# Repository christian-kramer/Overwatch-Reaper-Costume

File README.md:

# Overwatch-Reaper-Costume
Design files for Reaper's costume from Overwatch

---

This repo is my first for an actual "product" I've designed. It's a step forward in my exploration of embedded systems and circuit design, expanding on both my previous [Light Sensor](https://github.com/christian-kramer/Light-Sensor) and [STM32F407 Familiarization](https://github.com/christian-kramer/STM32F407-Familiarization) projects.

This project came about due to a need from a friend of some electronics and 3D models for a custom costume she was making: Reaper, from the videogame Overwatch.

Specifically, Reaper's dual shotguns. The requirements were:

1. All the red lights on the guns *(two spots underneath the barrel, one on the side-switch, one on the front underneath the barrels, and one near the top of the gun facing backwards towards Reaper)* need to be illuminated with a lighting effect accurate to the in-game look.
2. The barrels need to illuminate when the trigger is pulled, to mimic shots being fired.
3. Sound effects of a shot firing need to play every time the trigger is pulled, with no more than 4 shots per gun firing before the "reload" sound effect is played. Both guns need to reload at the same time, so if one is empty before the other, it needs to wait for the last shot to be fired from the other gun. Additionally, voice lines Reaper says in the video game after a kill need to play during the reload... making sure to play a different voice line each time.
4. Power is to be provided by two AA batteries per gun, due to space constraints in the handle.

So... Logically, thinking about this, I know I need some lights, a speaker, a radio, a microcontroller fast enough to handle the task of producing sound somehow, and a circuit board to hold everything together.

Cool! Sounds like a fun project. Let's start by figuring out what kind of lighting looks good.

LEDs are an obvious first thought, since they're so cheap and ubiquitous. But they're also very bright, and has a point-like look, even when diffused. Even after throwing everything I could think of at a standard 5mm red LED, I just couldn't get it to achieve the same look as the game. I tried thinking of other things that might produce a much deeper, richer red... A while ago, I had seen something cool on Adafruit called EL Wire, that might work. It's got a really, really nice effect:

But it requires a clunky inverter, and I'm dubious about how it'll show up in bright light.

I started looking around for other solutions, and stumbled upon this:

["Side-glow Fiber Optic Cable."](https://www.amazon.com/light-fiber-source-illuminator-Yellow/dp/B01M68WEUS) It looks great, and it's not electrical in nature! You can cut it to length, and whatever color LED you put into it is what you'll get out. So I ordered some, to try it out with the red LED. Unfortunately, it just wasn't bright enough. Too much light was being emitted from the sides of the LED, and not enough was going directly into the fiber optic cable. I was certain that if I could just get the LED to focus all of its energy into it, it would be bright enough. The first thing that comes to mind when trying to get light into a single point is a laser, so I started researching red laser diode modules and how to use them.

Turns out, all they need is 3 volts and a constant current supply of around 20 milliamps, and you can get [10 for $6.00 on Amazon](https://www.amazon.com/Laser-Diode-Module-650nm-10PCS/dp/B0166JFLES/ref=sr_1_3?keywords=laser+diode+module&qid=1562638198&s=gateway&sr=8-3) (with Prime, even!).

I ordered some, and I was blown away at how great it looked with the fiber optic cable!

My phone's camera doesn't do it justice. To the human eye, the light is perceived as very intense red. Not blindingly so, but it definitely looks a whole lot like what the video game shows for the lighting effects! I guess we're using lasers in our project.

A side-note about these laser modules: They're supposed to be supplied with an active constant-current power supply, but I found that a 22Ω resistor was plenty sufficient for stabilizing the current. These are for lighting effects, not scientific measurement.

My next step was to rip an existing solid 3D gun model off of thingiverse and hollow it out to find space for all the parts, and also figure out how to get the trigger to move instead of just being static like on the original model.

After much work figuring out how to make everything fit, and mount securely inside, I came up with this configuration:

In the handle are the two AA batteries, and behind the trigger is the microswitch I'm using to detect actuation and also provide the necessary "springiness" to give the feeling of a nice click when depressed. In blue is the speaker, positioned on a sliding tray above the decorative vent holes I drilled out to pass sound through to the outside world. Towards the front of the gun is the circuit board I still had yet to design, but I made it plenty big enough (8cm x 10cm) so that I should have no trouble fitting all the components I need onto it. On the circuit board, I modeled a little laser-holder to keep the side-glow fiber optic cable attached to the lasers, and the lasers attached to the board. Just a couple 3mm screw holes holding a couple clamshells together, with enough tension to make sure nothing moves. Simple, and easy to 3D print.

Speaking of circuit boards, I need to design one! But I need to figure out what to put on it first... I've got the lasers' chunk of real-estate dished out, but I still need to determine exactly what else I need to provision for. Well, I need a microcontroller to start. I think the ol' PIC10F220's out of the question for this one... I need something with a little more oomph. I remember really liking the STM32F407 when I was screwing around with my dev board, but that's probably a bit overkill for a project like this. I want a Goldilocks processor... so in the spirit of trying to use the bare minimum in my projects, and because I used a PIC in my last project, I'm going to look for a bottom-of-the-barrel STM32. Let's see what eBay's got.

I mean... that's nice and all, but that's still a lot of pins at a very high clock speed. I said bottom-of-the-barrel, darn it!

Now we're talking! It's not even in a quad flat package, it's dual-inline with only 20 pins! Let's load up CubeMX and see what it's got for features. (probably not a whole lot)

Actually, not bad! It's got an ADC, support for *both* I2C and SPI, 5 general-purpose timers plus a watchdog timer, and a real-time clock. Not bad for a 20-pin part. I think we have a winner for our microcontroller.

Also, as a bonus, dev boards are dirt-cheap.

Alright, I think now's a good time to tackle the hard part: sound.

I know that I use file formats like WAV and MP3 to store sound on my PC, but is any of that readable to a microcontroller of this simplicity? I needed to learn a lot more about how these formats work under the hood, and how other people have gone about playing sound on devices like the Arduino.

Apparently, since a WAV file is uncompressed, it represents what is called "PCM Audio", or "Pulse-Code Modulation Audio". This means that the bytes in a WAV file sequentially represent amplitude data of the audio waveform - the thing you see when you open something in Audacity or the like. Depending on the sample rate and resolution, this can be as simple as one byte representing an aplitude of anywhere from 0 to 255, played one after the other, 8000 times per second for an 8-bit, 8kHz audio file.

Here's a good visualization:

Each line is 1/8000 of a second apart (sample rate of 8kHz) and the value at each line can be anywhere from 0 to 255 (8-bit resolution). Turn those numbers into voltages that move a speaker cone, and baby, you've got audio.

Now how the heck do I get this thing to talk to a speaker? It certainly doesn't do so natively, like the STM32F407 does... gotta figure that one out on my own. Somehow, I need to get that waveform out to an amplifier. Most times, that's done with something called a Digital to Analog converter, or DAC, which you'll hear thrown around on various products' descriptions. But in the spirit of bare-minimum, I tried to see if I could use Pulse-Width Modulation combined with a filtering circuit to create the analog waves.

I'm just going to say right now, that I couldn't get that to work no matter how hard I tried. I'm going to have to bookmark that technique for later. For now, I'm saying "screw it" and using a DAC. But which DAC should I use?

A fairly popular one amongst the hobbyist community, produced in droves in China, is called the MCP4725. 

It's a nifty little thing, in the same size package as the the PIC10F220 I'm so familiar with. 12-Bit Resolution, rail-to-rail output which means it'll give me the full swing of 0v to 3.3v, and it supports High-Speed I2C which is more than enough to cover the 8kHz sample rate plus I2C frame data. Perfect! Now I gotta find an amplifier, because I really don't trust this thing to drive a speaker the size of what I need.

Now, every good EE has heard of the legendary LM386. Since 1969, it's been powering hobbyist and professional audio projects where "sounds good enough" reigns supreme. It's simple, yet versatile, and does what it's supposed to without a whole lot else. It takes an input, makes it louder, and gives you an output for an 8Ω speaker. If you need it even louder, put a capacitor between pins 1 and 8. Sound too staticy? Put a capacitor between pin 7 and ground. Boom, done. Loud. Happy? Good.

These chips are so common, even the knockoffs have knockoffs. You can buy buckets of them for next to nothing, which makes them great for this project and possibly future ones since I'll probably have plenty laying around.

One problem, though... It needs a minimum of 4v to work, and everything else I've got is 3.3v. Looks like I need two power rails... remember that, for later.

Wait, sorry, I see two problems... the LM386 input is expecting a voltage between 0 and 0.4v, not 0 and 3.3v like my DAC is putting out. Anything above 0.4v is going to get clipped, which means I need to figure out how to scale the audio. I want to make use of the full 12-bit resolution of the MCP4725, so I'm thinking maybe scaling the output of the DAC using some analog circuitry before it gets to the LM386 might be a good idea.

A common tactic for scaling an analog signal like this is to use two resistors in a configuration called a "voltage divider".

If we want 3.3v (the upper limit of the DAC) to correspond with 0.4v (the upper limit of the amplifier input), and we start with a known resistor value of 150kΩ for Z1 (because that's a standard resistor value that I know is produced), we get a nominal Z2 value of 20.69kΩ, which is not a standard resistor that is produced. Luckily, 20kΩ is, and that's "close enough for government work."

I'd also like to explain why I'm choosing resistors in this range of values... the answer, is because I just need a voltage reference for the LM386. I don't want to waste unnecessary battery power heating up resistors, but I also don't want so much resistance that the voltage reference isn't responsive enough for my purposes. These are in a sweet spot between both.

So after all of my dev boards arrived in the mail, and I pulled an LM386 out of an old door alarm, I ended up building this:

The STM32 communicates over High-Speed I2C to the MCP4725, which outputs the PCM WAV file to voltages anywhere between 0 to 3.3v depending on the wave amplitude at that "frame" of the sound file. That 0 to 3.3v signal gets coupled to the voltage divider in the reverse-"L" shape by a 10nF capacitor to help smooth out the "jumps" in the 8kHz audio, then finally gets sent to the LM386 input pin. The LM386 output pin gets coupled to the 8Ω speaker by a pretty big capacitor. Here, I'm using a 330µF electrolytic to remove the DC bias from the amplifier, so the speaker cone goes through its whole range of motion. Additionally, I put a high-pass filter on the output pin to chop off some unwanted low-frequency noise.

The sound file itself is stored on the STM32, compiled from a C character array that I just iterate through 8000 times per second in a for loop.

Unfortunately, due to how small the storage on-board the STM32 is, I found only one voice line of Reaper's that was short enough to fit on it! In order to store *all*  of them, I'm going to need some external storage.

I thought to myself... "Hm... flash storage has been getting pretty dense and cheap, lately. I wonder what kind of chips are out there that might store the amount of data I'm looking for."

I looked into Micro SD Cards, but even for a 2GB card it took over 100 milliamps! Holy cow, I don't have that kind of overhead with these two AA batteries! And 2GB is *way* overkill for what I need. I had to find something smaller, and lower-power.

Eventually, my friend ended up finding this:

The Macronix MX25L1606EM2I, a 2MB SPI flash chip capable of exchanging data at very high speeds, at very low power. The cool thing about SPI flash chips is that their form factor is pretty much standardized, as well as their pinout and (for the most part) their instruction set... so in the future, if I theoretically wanted to switch out this chip for a larger one, or a different manufacturer, it should be a drop-in replacement. Pretty convenient!

But unlike a Micro SD Card, I can't just plop this into my PC and drag files onto it... This is just bare memory, I needed to be able to talk to it somehow.

Looking around on eBay, I found a pretty highly-rated Flash IC programmer that supported both SPI and I2C chips called the CH341A.

The MX25L1606EM2I can't plug directly into the ZFI socket on the programmer, so I made sure to find one that included this little "clamp" to hold onto the 8 pins of the flash chip.

The software for it looks like this:

And I gotta say, after changing the language from Chinese, it was pretty much plug-and-play. (With the exception of the diagram in the lower left being WRONG! The chip should be rotated 180 degrees, in that same 8-pin slot.) The programmer talked to the chip just fine, and I could key-in values at whatever memory addresses I wanted.

So... I got the chip to talk to my computer, and store data successfully. But how about reading it from the microcontroller?

Reading into the datasheet, the command structure for reading from the chip is:

1. Pull the Chip-Select pin low.
2. Send it `0x03` in the first byte of data. This is to instruct the chip that we intend to read from it, and we are about to give it an address in the next 3 frames.
2. Send it the first byte of the 6-byte address.
3. Send it the second byte of the 6-byte address.
4. Send it the third byte of the 6-byte address. Note: after these are all sent, the chip will start reading off not only that byte, but every consecutive byte until it reaches the end.
5. Finally tell it to shut up by pulling the Chip-Select pin high.

And that, in theory, should work. There's two other pins on the chip that are of interest: Write-Protect, and Hold. Write-Protect does what you'd expect, and Hold stops the entire chip from doing anything. From my adventures diving into EE forums, I learned that those pins aren't necessary for normal operation, and can just be left unconnected.

But... when I tried reading a memory address on the flash chip from the STM32, it wouldn't respond! I was getting no data back at all!

So, to troubleshoot, I hooked the chip back up to the CH341A, but this time using DuPont jumper wires, and verified that it could talk to the PC. Then, I pulled the Write-Protect jumper out to see if that was the culprit... No dice, the flash chip was still acting normally. Next, I pulled the Hold jumper out... and bingo! I got a Read Error from the software saying that the chip wasn't responding.

So, instead of leaving Hold unconnected like I originally did, I tried tying it to ground with that jumper... And the read error went away! It was behaving normally again.

On the microcontroller side of things, I tried using another jumper to tie Hold to ground while leaving Write-Protect floating... and suddenly, I got the byte of data I was expecting!

My breadboard prototype now looked like this:

After uploading a larger WAV file to the flash chip than would fit on the STM32, I tried reading each byte and outputting it to the DAC fast enough to play the voice line. The result was actually pretty promising, and sounded decent considering the mediocre speaker I was using.

Next challenge: the radio.

So, after a cursory glance at what other people are using for their low-cost RF needs for Arduino  projects and whatnot, I was consistently pointed towards the nRF24L01 module.

These are about a buck a pop on Amazon, with Prime shipping included. Interestingly enough, these *also* communicate over SPI... which means I now have to make sure that the MX25L1606EM2I and nRF24L01 will play nice together on the same line. After all, with the Hold pin needing to be tied to ground, which it shouldn't have to be, it very well may not.

See... SPI isn't addressed. You have to expressly tell each chip, "HEY! I'm talking to you." And sometimes, when finished talking to that chip, it won't release the MISO line like it's supposed to, which prevents other chips from talking.

SD Cards are apparently notorious for exhibiting that behavior when operating in SPI mode, so... yeah, I'm glad I didn't use one on this project.

A common workaround for this is to put a device called a "tri-state buffer" on the problem device, which then forcefully disengages the MISO line for that device when the Chip-Select line goes high, thus allowing other devices to talk.

So the only way to figure out if the MX25L1606EM2I was a problem device, was to try it on the same SPI line as the nRF24L01.

I tacked on a radio module to my breadboard, and whipped up a little battery-powered stand-alone nRF24L01 + STM32 project.

Then, I wrote some code that did the following:

1. Battery-powered module transmits to waiting sound-breadboard module that it should start playing the soundbyte from the flash chip, which is indicated by the blue LED on the sound-breadboard module turning on.
2. The sound-breadboard module instantly transmits back to the battery-powered module to turn on its LED, indicating that bidirectional communication is possible.
3. After the soundbyte finishes playing on the sound-breadboard, it instructs the battery-powered module to turn off its LED. This indicates a successful handover from radio, to flash chip, to radio... I.E. both devices are capable of releasing the MISO line without issue.
2. Once the battery-powered module has turned off its LED, it instantly instructs the sound-breadboard module to do the same.

The result of these four transactions should yield two devices that turn on, and off their LEDs seemingly in perfect synchronization, while also proving that neither device is holding the MOSI line hostage.

And... here it is in action:

[Dual-SPI Device Test Video](https://i.gyazo.com/60b7cc6970f24641ac8ad5783b88ba2e.mp4)

Success! No tri-state buffer needed.

Additionally, to improve sound-quality, I added some more filtering on the output pin. For such low-cost and low-power parts, it was starting to sound *really* good... and loud!

This pretty much constituted the entirety of the project... sound, lights, bidirectional communication... I feel like I'm forgetting something, though.

Oh, right. Power.

Yeah, I forgot... I gotta run *all this* off of just 2 AA batteries. Since I need 3.3v for most of my electronics, and 5v for the LM386, but the AA batteries provide *at most* 3v... I need to boost the voltage somehow.

I did some digging for any battery-management chips that may exist, that are cheap enough for my project... and stumbled upon a magical unicorn called the AAT1217.

Easy-to-use with just 6 pins, an external inductor, and some resistors to set the output voltage (and an external schottky diode if you're setting it above 4.5v), this baby will squeeze every last drop of juice out of your choice of either a single AA battery, two AA batteries, or a single disposable Lithium-Ion battery, with up to 93% efficiency... all in the same package as the PIC10F220 and the MCP4725. Perfect!

My strategy was to set this to 5v to supply the LM386 with what it needs, and then use a linear regulator to step it back down to 3.3v. In the grand scheme of things, that's a trivial change, and any regulator worth its salt should be able to handle that with almost no energy loss.

My regulator of choice: AMS1117

Funny enough, these things are in the dev boards I ordered... as well  as like, every Arduino ever made. Pretty common, and very cheap!

With all this planned out, I set to work creating the schematic for the whole circuit board. Something I made sure to include was a jumper to cut power to all the lasers, so that I could completely remove the risk of damaging my eyes when I was working on the board.

Dang, that's a whole lot more complicated than my first board design. Time to lay it out!

I tried to compartmentalize different parts... power in the lower right, audio amplifier in the top right, all the connectors on the right edge so they point towards the back of the gun... laser holder on the bottom, with 3mm drill holes... 5 connectors, all in a row for the 5 lasers, with the one that can be blinked marked with a \*. I had trouble routing all the traces away from the STM32, so I flipped it to the backside of the board and broke it out with a bunch of vias, so I had enough room to work.

After a few weeks, the boards arrived in the mail:

Fun fact: Matte Black doesn't cost any more than Green, at JLCPCB. Man, it looks good! And the CK is so shiny...

Because these boards are so complex, and I never tested the AAT1217 before designing it in... I decided it would be best to assemble this in parts, starting with the lower right power circuitry and the lasers.

And... Hey! It works!

This was with fresh batteries, supplying very nearly 3v... But for fun, I tested this with batteries that wouldn't even run my analog wall clock, and the laser powered up just fine at the same brightness as the fresh batteries. Whether or not the amplifier will still work with batteries this dead remains to be seen.

The next parts of the board, I assembled in steps. The very next thing I soldered was the STM32. I wanted to make sure that was getting clean enough power to talk to the ST-Link, over the programming header on the board. The "RST" pin you see towards the bottom of the header isn't actually needed. I included it just in case I needed to force-reset the chip for any reason, but during normal programming/debugging operation, the STM32 accepts a "software reset" - a special sequence of bits that tells the internal firmware of the STM32 that it's time to  go into reset mode. When powered off the batteries, the ST-Link only needs 3 wires: DIO, CLK, and GND.

Next was the MCP4725 and associated 4.7kΩ I2C pull-up resistors. I wanted to make sure that, before I assembled the amplifier, I was getting a good output from the DAC to limit how much troubleshooting I'd have to do, should this board not produce sound as expected.

After I verified that the MCP4725 was outputting the voltages I told it, at speeds comparable to what I need for clear audio, I went ahead and assembled the  amplifier. I had a test from earlier that I already made to play a small soundbyte from the internal STM32 flash... After loading that up, and plugging in the speaker... it sounded great!

Now that I knew sound worked at the most basic level, I knew I could go ahead and get the flash chip programmed with all the voice lines, and try playing WAV files from that.

Essentially, I just stacked everything together end-to-end... but I knew that by just doing that, it'd be hard to see in the hex editor where individual soundbytes were in the file. So, I came up with a way to delineate each one by driving the amplitude up to 255 between each voice line. In audacity, it looks like this:

In the hex editor, it looks like this:

That wall of FF's you see there is my marker for where the sound data ends, and at the end of the wall is the next voice line. It continues on past the bottom of the window a bit, so it's impossible to miss while I'm scrolling. This way, I've eliminated guesswork for where each individual sound file is located... and I don't have to re-guess if I decide to switch out or remove a voice line from the chip. It's plain-as-day to see what I'm working with. Also, to quash any concerns about "wasting bytes"... These voice lines barely use 1/4 of the chip's total capacity. I've got plenty of room to spare for making things easy for myself.

After proving that I could play audio from the chip through the DAC and amplifier... I moved on to soldering the radio onto the SPI bus. Once the radio was on, I loaded up another program of mine that tests bidirectional communication with another radio on a breadboard, to trigger playing a sound file. Something unusual happened, though... Unlike my breadboard tests with an (in theory) identical circuit, the assembled board refused to transmit back to the other radio, after the sound file finished playing. "This is odd," I thought, because in the program, it's supposed to wait for the broadcast... What's going on?

My initial thought was that the power requirements were too much... but the issue persisted even *after* I unplugged the speaker. What gives? My next thought was that maybe I really did need that tri-state buffer, after all. Unpredictable chips causing weird behavior, and such... But after some tests with reading the status register of the nRF24L01, I proved that the flash chip was handing over control of the MISO line like it should. What in the world was going on here?! Faulty radio? Using my breadboard prototype, I was quickly able to test all 9 other radios in my pack of 10 from Amazon, and all worked just fine. The likelihood that I picked the single bad one at random from the bag was too small for me to really consider... Due to the proximity of the radio's pins to the flash chip, it would be too  risky to remove it... So I opted to try using jumper wires to test the radio I had soldered onto my board. I had difficulty getting one jumper on the MISO pin, due to a glob of solder getting in the way. After heating it up, and moving it down to the base of the pin, an idea popped into my head: "What if that just fixed it, right there?"

So I turned it on, and boom! Bidirectional communication restored. All it was, was a bad solder joint on one of the data pins! What a relief. With that final outlying problem solved, I had in my hands an (almost) fully working board. All that was left was to get the LEDs, transistors, and the Trigger connector soldered, and crimp some more JST connectors onto my lasers!

Next, I needed to get the front-facing LEDs, transistors, and trigger switch port added on.

Oddly enough, I think the transistors ended up being the most difficult part to solder by far. I've actually never soldered a TO-92 package component before, so I was woefully unprepared for the challenges I encountered. These things dissipate as much heat as possible by design... and when a glob of solder comes into contact with one of the legs, it pretty much instantly cools and solidifies before it has a chance to bond with the board. This leaves you with legs that *look* soldered... but actually have no electrical contact with the board whatsoever, and can be moved as easily as a loose tooth. Reworking is almost impossible, because any heat you add to the problem-solder gets immediately transferred to the transistor casing. Too much heat kills the transistor, which means you have to heat it up an absurd amount to get the solder glob to even budge. Adding more solder to try to rectify the problem doesn't work either, because I've found it almost always ends up contacting a neighboring pad.

I learned all this after killing around 6 transistors on the second board, trying to get them to stick.

When you do kill a transistor by trying to solder it too much, it is extremely difficult to remove. Because the legs cool very quickly, pulling the entire length out through the hole isn't really an option. I had to resort to cutting the legs as short as possible, and then simultaneously heating them up, and torquing them through with brute force. Actually, on that second board, a fragment of the Base pin of a broken transistor got permanently stuck in the hole, and I was forced to solder the new leg directly to the resistor.

As far as soldering the rest of the legs... I came up with a technique that seemed to work pretty reliably, and it's one that I'll likely use for future TO-92 soldering; if you cut the legs flush with the holes *before* soldering, and just "cap" each one with a small glob of solder... it mitigates almost every issue mentioned above. You still only get "one shot," and it still has a good chance of making contact with a neighboring pad, but it's the best I've been able to come up with so far.

After this was all said and done with, I fired up the second board to make sure it worked as intended. But... it didn't, in one very weird aspect. One of the LEDs on the front was really, really dim when it was supposed to be off... and only got *dimmer* when it was supposed to be on! What in the world?! I was convinced I had managed to solder the transistors withoug killing them, this time... so what was happening? I measured the voltage at the base resistor of both of the other transistors... 3.3v, just as they should be. Then, I measured it at the base resistor of the problem transistor... 0v! The problem must be up-stream somewhere. Is the other end of the resistor getting 3.3v? Yes... and that goes directly to the microcontroller. And... that pin looks fine, from a quick visual inspection. Uh oh, did my transistor-shenanigans end up killing a GPIO pin? A quick reading of the pin with my multimeter shows that it's putting out 3.3v on command... so, no, it's fine. Must be a problem with the pad. But, quickly checking the continuity of the resistor showed that it was good all the way through! How could this be?!

After much troubleshooting, the answer was a little embarrassing... the very, *very* slight pressure from the multimeter probe was forcing the pin to make contact with the pad, and give a false impression of reliable continuity. One swipe from my fine-tipped soldering iron connected the pad properly, and the LED lit up and turned off just fine.

That's the one thing I really dislike about these STM32s... The dual-inline package has such fine pins that it seems to almost never go down without needing some sort of tedious rework. I'll have to try out a quad flat package in a future project to see if that's easier.

In the meantime, I've also figured out an even easier/more reliable method of soldering TO-92's... just use solder paste, and heat them up like you would an SMD component. The solder paste flows exactly where it needs to, and provides a very secure bond with the board. No hassle, and almost guaranteed to not kill the transistor.

Eventually, I got all 4 boards finished up, and ready to program! Still gotta finish all those lasers and cables up, though.

Meanwhile on the mechanical side, things were (literally) starting to take shape.

Here are the bottoms of the handles that house part of the trigger assembly, and form the very bottom of the battery housing...

And here are some various small parts for the internals of the gun, like the Speaker Tray, PCB Tray, the two halves of the 5-Laser-Holder that mounts to the two holes on the PCB, and some general support material.

Some bigger parts have also been printed, such as one half of the front barrel which houses the PCB, and the decorative handle on the back.

Inside, the slot for the tray, and the cavity for the front-facing fiber optic cable look great!

Back to PCB-land for a moment; it's firmware time!

Now, the only human interface our guns have is the trigger... so that means that the logical distinction of which of the two boards is in charge of making decisions like what channel to communicate on, when to reload, and which voice line to play after the reload needs to be made in software, and not with a jumper or DIP switch or something.

The best way I could think of to describe how the two boards need to behave was to make a flowchart:

What I've made here is called a "Finite-State Machine", which is a machine that can be in exactly one of a finite number of states at any given time. This computational paradigm is, in practice, insanely reliable and thus used extensively in industrial automation and "black-box" consumer electronics.

Check out my [`main.c`](https://github.com/christian-kramer/Overwatch-Reaper-Costume/blob/master/Electrical/Source/Main%20Firmware/Src/main.c) showing how I implemented this logic. Commented to enhance readibility.

And, to see this whole thing in action, check out this video I made of all 4 boards operating in the same general vicinity with no interference:

[https://youtu.be/M1ywswBbeoI](https://youtu.be/M1ywswBbeoI)

With the electronics completed, it was back to getting all the parts 3D printed.

A second 3D printer was purchased to help cope with the amount of printing, an Ender 3 Pro by Creality. After some setup, it was off to the races (for only $200!)

Eventually, all the pieces needed for one of the guns were printed!

It was time to do a test fit to see how everything went together. While it looks like a very complicated assembly process, the pieces are actually quite intuitive to put together since they're all so unique.

See, very simple. It's not glued together yet, this is just a test-fit to see how it all sizes up and if there's any parts that need a little TLC. But everything fit nice and snug, and lined up the first time!

And, of course, ruler for scale:

Other parts for the costume started to get printed as well, like various pieces of Reaper's 4 belts:

And, here it is for size:

Next, it was time for sanding and a round of paint! Time to make these pieces *really* look good!

Before:

After:

Black was the chosen base coat, to be followed by silver in applicable areas.

Together, they make a really neat effect!

All of the parts came out really shiny, and they look amazing.

Next, it was time for the big prints! The gauntlets were to be printed in two parts... a smaller, lower wristpiece... and a gigantic upper forearm piece that would take many hours and have a relatively high probability of failure.

But... dang! Fresh off the printer, the first one looks amazing! It's a little angular due to having to manually stitch some polygons together in Cinema 4D, but that'll clean up after some sanding.

So, arms are coming along nicely, but now it's time for the legs! We've got some boots to make. But I don't feel like making a boot from scratch, so let's find an existing pair to build off of. We had an old pair of motorcycle boots that resembled the shape of Reaper's boots that we could add parts to. But... the parts in their current form won't fit the boot perfectly, and I'm not willing to sit there printing adjustment after adjustment just to hone in on the right shape. I need to know that the part I'm printing is going to fit, 100%. So, how do we do this?

An idea I had was to use photogrammetry to "scan" the boots into Cinema 4D, and then mold the pieces virtually before printing.

We took video of all angles of the boots to give Agisoft Photoscan every possible detail to work off of. In After Effects, I keyed out the pink backdrop to generate an alpha channel mask for every frame of the video, which was then exported as a PNG sequence with alpha channel. That gave us about 1000 camera angles to work with, which in my experience should be plenty to get an accurate model.

After a few nights of computation, Photoscan spit this out:

Beautiful! I can work with this.

After a bit of work, I made this in Cinema 4D:

Yeah, it clips a little bit... but boots aren't completely solid, so these parts should fit.

And... It definitely looks like they will! No wasted PLA plastic here. This method totally works!

Meanwhile, while all this is going on, the PCBs have arrived at their final destination and are ready to be mated to the 3D printed gun for the first time.

And... there it is! Sound works, the LEDs line up with the barrels properly, and it's definitely loud and bright enough!

The connection between the radio and microcontroller on the PCB is a little shaky, though, which is something I encountered on my bench tests... It may be necessary to do a "revision 2" of the boards in order to remedy the issue and make it more reliable.

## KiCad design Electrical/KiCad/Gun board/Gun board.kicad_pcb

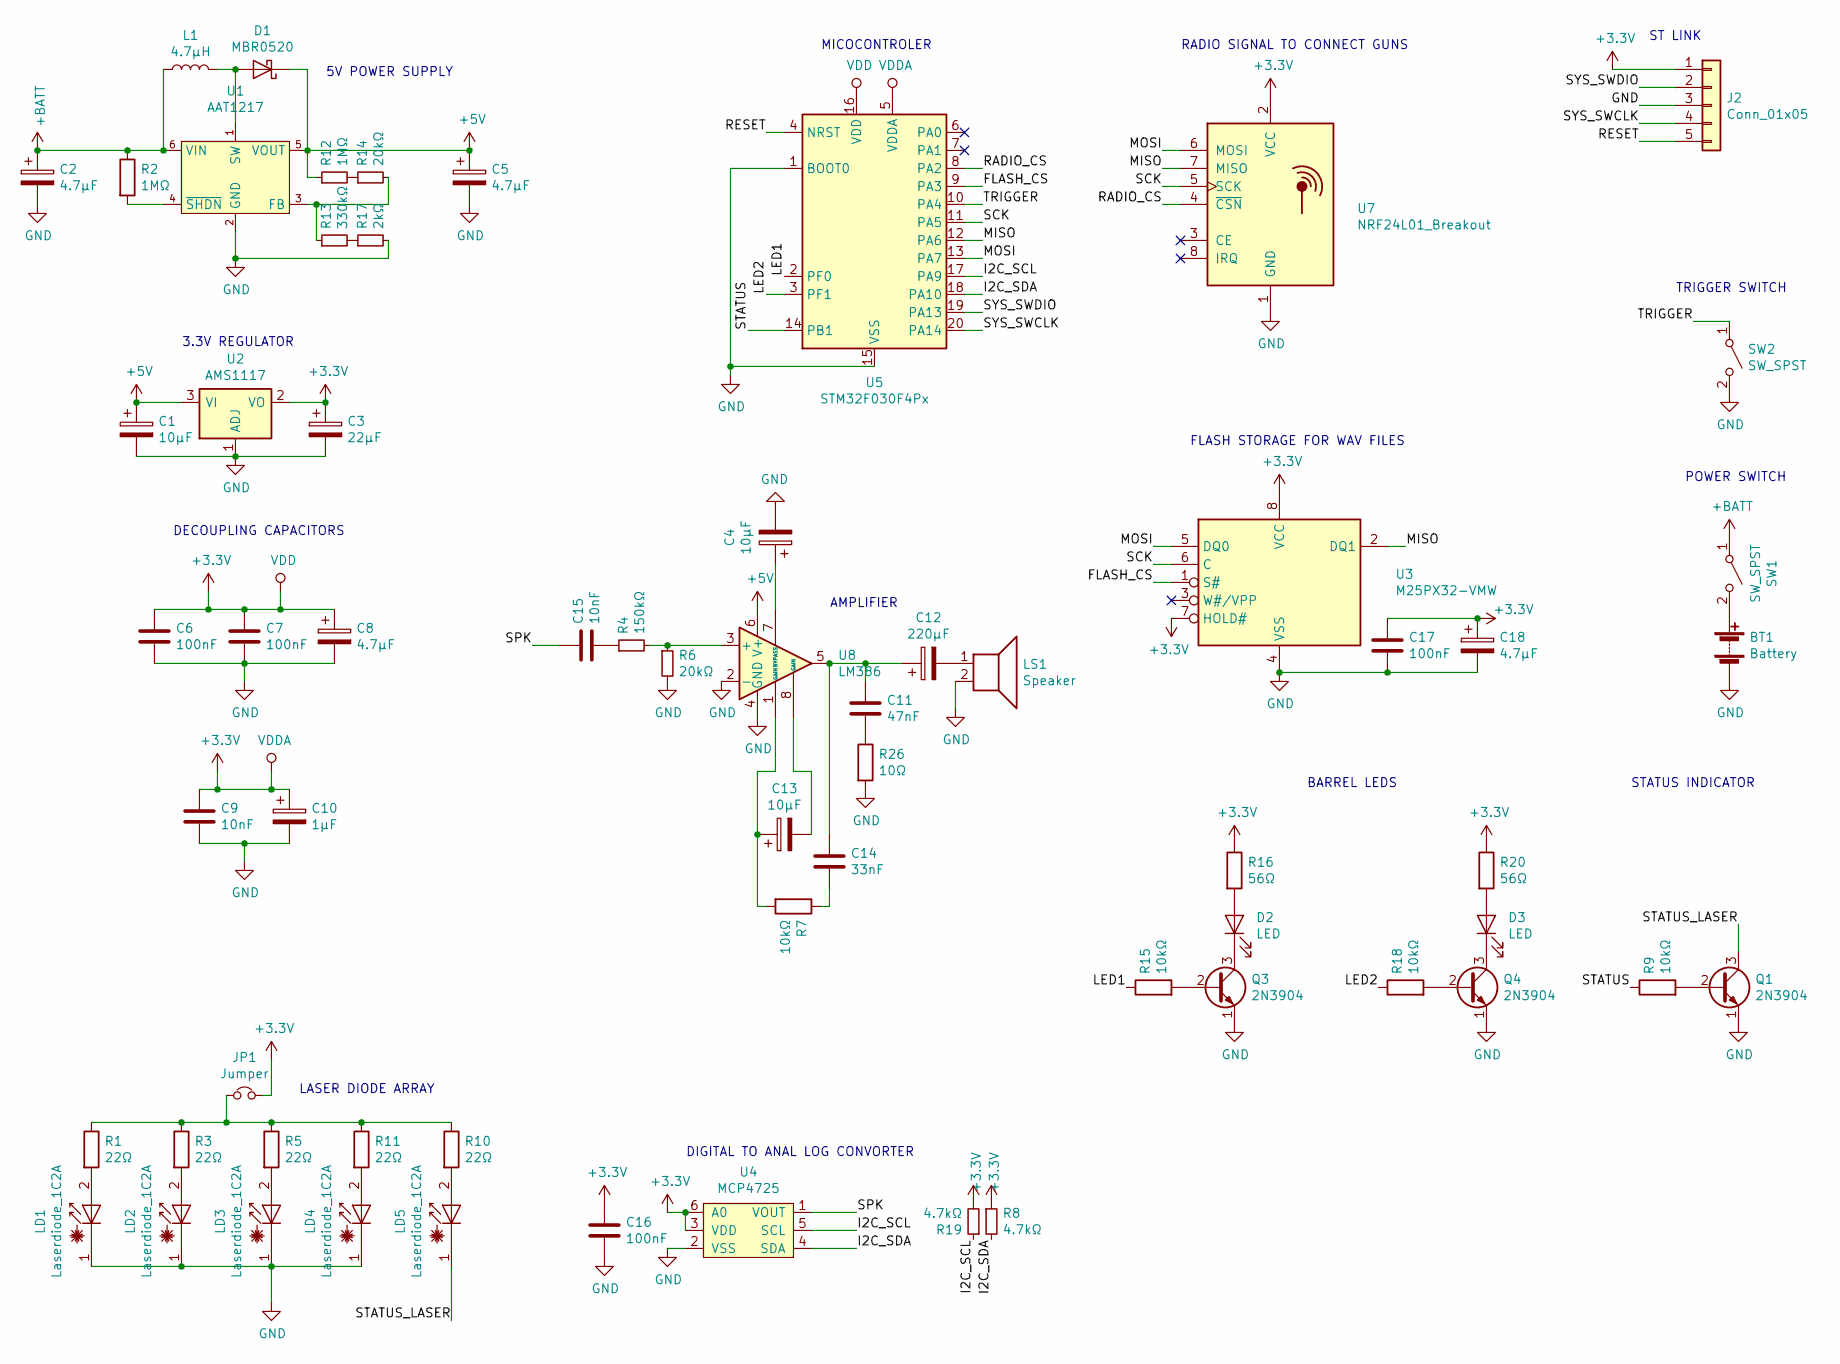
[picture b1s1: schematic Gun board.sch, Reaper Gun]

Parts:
BT1: Battery; JST_PH_S2B-PH-K_1x02_P2.00mm_Horizontal
C1, C4, C13: 10μF; CP_Elec_5x5.4
C2, C5, C8, C18: 4.7μF; CP_Elec_4x5.4
C3: 22μF; CP_Elec_6.3x5.4
C6, C7, C16, C17: 100nF; C_0805_2012Metric
C9, C15: 10nF; C_0805_2012Metric
C10: 1μF; CP_Elec_4x5.4
C11: 47nF; C_0805_2012Metric
C12: 220μF; CP_Elec_8x10.5
C14: 33nF; C_0805_2012Metric
D1: MBR0520; D_SOD-123
D2, D3: LED; LED_D5.0mm
J2: Conn_01x05; PinHeader_1x05_P2.54mm_Vertical
JP1: Jumper; PinHeader_1x02_P2.54mm_Vertical
L1: 4.7μH; L_TracoPower_TCK-141
LD1, LD2, LD3, LD4, LD5: Laserdiode_1C2A; JST_PH_B2B-PH-K_1x02_P2.00mm_Vertical
LS1: Speaker; JST_PH_S2B-PH-K_1x02_P2.00mm_Horizontal
Q1, Q3, Q4: 2N3904; TO-92_Inline
R1, R3, R5, R10, R11: 22Ω; R_0805_2012Metric
R2, R12: 1MΩ; R_0805_2012Metric
R4: 150kΩ; R_0805_2012Metric
R6, R14: 20kΩ; R_0805_2012Metric
R7, R9, R15, R18: 10kΩ; R_0805_2012Metric
R8, R19: 4.7kΩ; R_0805_2012Metric
R13: 330kΩ; R_0805_2012Metric
R16, R20: 56Ω; R_0805_2012Metric
R17: 2kΩ; R_0805_2012Metric
R26: 10Ω; R_0805_2012Metric
SW1, SW2: SW_SPST; JST_PH_S2B-PH-K_1x02_P2.00mm_Horizontal
U1: AAT1217; SOT-23-6
U2: AMS1117; SOT-223-3_TabPin2
U3: M25PX32-VMW; SOIJ-8_5.3x5.3mm_P1.27mm
U4: MCP4725; SOT-23-6
U5: STM32F030F4Px; TSSOP-20_4.4x6.5mm_P0.65mm
U7: NRF24L01_Breakout; nRF24L01_Breakout
U8: LM386; SOIC-8_3.9x4.9mm_P1.27mm

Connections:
+3V3: C3.1, C6.1, C7.1, C8.1, C9.1, C10.1, C16.1, C17.1, C18.1, J2.1, JP1.2, R8.1, R16.1, R19.2, R20.1, U2.2 (VO), U3.7 (HOLD#), U3.8 (VCC), U4.3 (VDD), U4.6 (A0), U5.5 (VDDA), U5.16 (VDD), U7.2 (VCC)
+5V: C1.1, C5.1, D1.1 (K), R12.1, U1.5 (VOUT), U2.3 (VI), U8.6 (V+)
+BATT: C2.1, L1.1, R2.1, SW1.1 (A), U1.6 (VIN)
/FLASH_CS: U3.1 (S#), U5.9 (PA3)
/I2C_SCL: R19.1, U4.5 (SCL), U5.17 (PA9)
/I2C_SDA: R8.2, U4.4 (SDA), U5.18 (PA10)
/LED1: R15.1, U5.2 (PF0)
/LED2: R18.1, U5.3 (PF1)
/MISO: U3.2 (DQ1), U5.12 (PA6), U7.7 (MISO)
/MOSI: U3.5 (DQ0), U5.13 (PA7), U7.6 (MOSI)
/RADIO_CS: U5.8 (PA2), U7.4 (~CSN)
/RESET: J2.5, U5.4 (NRST)
/SCK: U3.6 (C), U5.11 (PA5), U7.5 (SCK)
/SPK: C15.1, U4.1 (VOUT)
/STATUS: R9.1, U5.14 (PB1)
/STATUS_LASER: LD5.1 (K), Q1.3 (C)
/SYS_SWCLK: J2.4, U5.20 (PA14)
/SYS_SWDIO: J2.2, U5.19 (PA13)
/TRIGGER: SW2.1 (A), U5.10 (PA4)
GND: BT1.2 (-), C1.2, C2.2, C3.2, C4.2, C5.2, C6.2, C7.2, C8.2, C9.2, C10.2, C16.2, C17.2, C18.2, J2.3, LD1.1 (K), LD2.1 (K), LD3.1 (K), LD4.1 (K), LS1.2, Q1.1 (E), Q3.1 (E), Q4.1 (E), R6.2, R17.2, R26.2, SW2.2 (B), U1.2 (GND), U2.1 (ADJ), U3.4 (VSS), U4.2 (VSS), U5.1 (BOOT0), U5.15 (VSS), U7.1 (GND), U8.2 (-), U8.4 (GND)
unnamed: BT1.1 (+), SW1.2 (B)
unnamed: C4.1, U8.7 (BYPASS)
unnamed: C11.1, C12.1, C14.1, U8.5
unnamed: C11.2, R26.1
unnamed: C12.2, LS1.1
unnamed: C13.1, R7.2, U8.1 (GAIN)
unnamed: C13.2, U8.8 (GAIN)
unnamed: C14.2, R7.1
unnamed: C15.2, R4.1
unnamed: D1.2 (A), L1.2, U1.1 (SW)
unnamed: D2.1 (K), Q3.3 (C)
unnamed: D2.2 (A), R16.2
unnamed: D3.1 (K), Q4.3 (C)
unnamed: D3.2 (A), R20.2
unnamed: JP1.1, R1.1, R3.1, R5.1, R10.1, R11.1
unnamed: LD1.2 (A), R1.2
unnamed: LD2.2 (A), R3.2
unnamed: LD3.2 (A), R5.2
unnamed: LD4.2 (A), R11.2
unnamed: LD5.2 (A), R10.2
unnamed: Q1.2 (B), R9.2
unnamed: Q3.2 (B), R15.2
unnamed: Q4.2 (B), R18.2
unnamed: R2.2, U1.4 (~SHDN)
unnamed: R4.2, R6.1, U8.3 (+)
unnamed: R12.2, R14.1
unnamed: R13.1, R14.2, U1.3 (FB)
unnamed: R13.2, R17.1

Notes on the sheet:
LASER DIODE ARRAY
ST LINK
BARREL LEDS
DECOUPLING CAPACITORS
RADIO SIGNAL TO CONNECT GUNS
MICOCONTROLER
5V POWER SUPPLY
AMPLIFIER
DIGITAL TO ANAL LOG CONVORTER
STATUS INDICATOR
3.3V REGULATOR
FLASH STORAGE FOR WAV FILES
TRIGGER SWITCH
POWER SWITCH

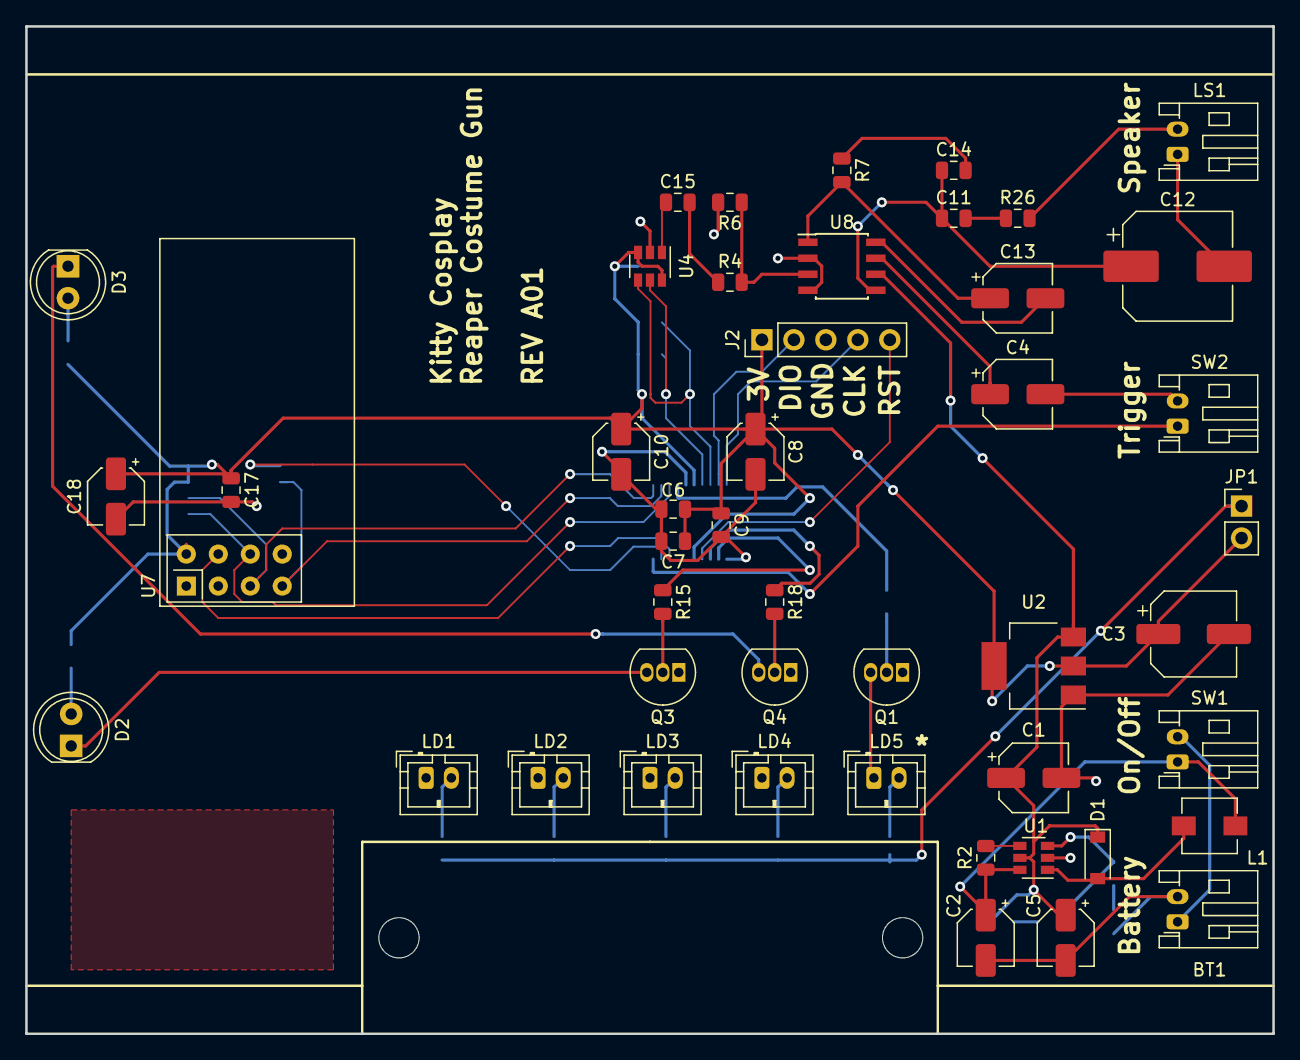
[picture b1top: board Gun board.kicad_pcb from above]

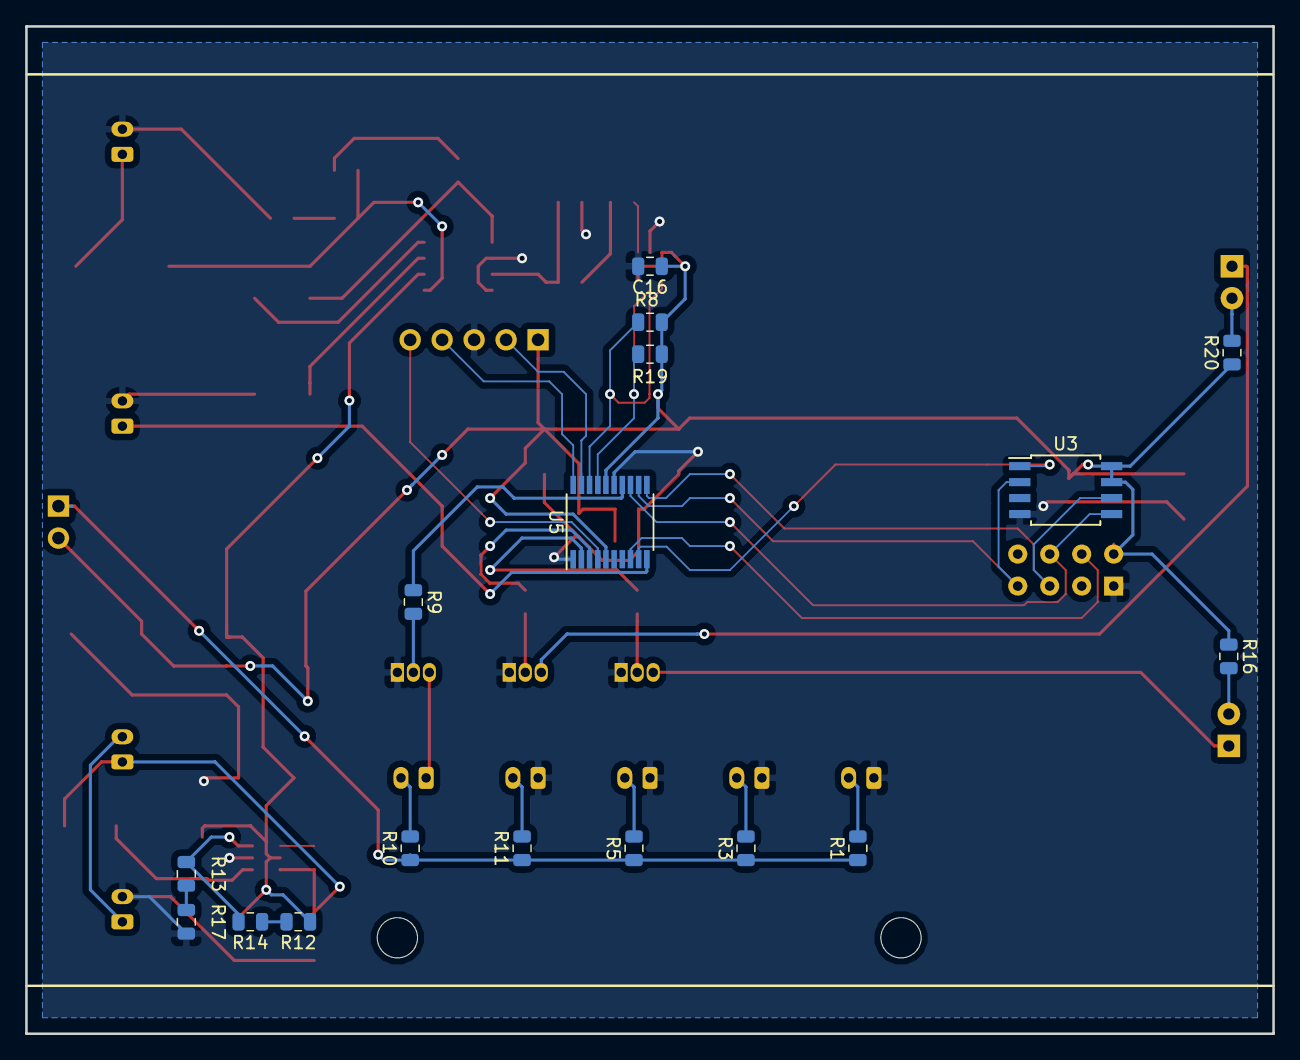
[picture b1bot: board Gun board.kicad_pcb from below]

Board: 2 copper layers, 99.1 x 80.0 mm, 64 parts (17 on the bottom side), 48 nets.

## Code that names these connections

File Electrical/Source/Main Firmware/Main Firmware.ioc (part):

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Mcu.Name=STM32F030F4Px
Mcu.Package=TSSOP20
Mcu.UserName=STM32F030F4Px
PA10.Mode=I2C
PA10.Signal=I2C1_SDA
PA13.Mode=Serial_Wire
PA13.Signal=SYS_SWDIO
PA14.Mode=Serial_Wire
PA14.Signal=SYS_SWCLK
PA2.GPIOParameters=GPIO_Speed,GPIO_Label
PA2.GPIO_Label=Radio_CS
PA2.GPIO_Speed=GPIO_SPEED_FREQ_HIGH
PA2.Signal=GPIO_Output
PA3.GPIOParameters=GPIO_Speed,GPIO_Label
PA3.GPIO_Label=Flash_CS
PA3.GPIO_Speed=GPIO_SPEED_FREQ_HIGH
PA3.Signal=GPIO_Output
PA4.GPIOParameters=GPIO_PuPd,GPIO_Label
PA4.GPIO_Label=Trigger
PA4.GPIO_PuPd=GPIO_PULLUP
PA4.Signal=GPIO_Input
PA5.Mode=Full_Duplex_Master
PA5.Signal=SPI1_SCK
PA6.Mode=Full_Duplex_Master
PA6.Signal=SPI1_MISO
PA7.Mode=Full_Duplex_Master
PA7.Signal=SPI1_MOSI
PA9.Mode=I2C
PA9.Signal=I2C1_SCL
PB1.Signal=GPIO_Output
PF0-OSC_IN.GPIOParameters=GPIO_Label
PF0-OSC_IN.GPIO_Label=Bottom_LED
PF0-OSC_IN.Signal=GPIO_Output
PF1-OSC_OUT.GPIOParameters=GPIO_Label
PF1-OSC_OUT.GPIO_Label=Top_LED
PF1-OSC_OUT.Signal=GPIO_Output
RCC.SYSCLKFreq_VALUE=28000000
RCC.SYSCLKSource=RCC_SYSCLKSOURCE_PLLCLK
board=custom

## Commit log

2019-04-04 testing
2019-04-04 Initial commit of current working files
2019-04-05 starting clean with original STL files
2019-04-05 testing sizing for the scale of the gun
2019-04-05 Provisioned pins according to block diagram
2019-04-05 Created overview diagram of project
2019-04-10 added pin assignment for 5v rail shutoff
2019-04-10 small-revision ready to print
2019-04-11 split large prints in half to reduce print time
2019-04-12 reorganized files and created cartridge
2019-04-12 added cap to cartridge and o-rings for seal
2019-04-14 reconstructed the cap of cartridge
2019-04-14 started working on electrical for gun model
2019-04-14 modifications for printing
2019-04-15 added 3v power symbol
2019-04-15 created 5v, 3v3, and 3v regulator circuits
2019-04-15 added power decoupling and nets
2019-04-17 added current-limiting resistors to laser diodes, jumper to laser diode power supply
2019-04-17 added NRF24L01 breakout module
2019-04-17 Created TCA6507 Component
2019-04-17 Switched LED Driver IC to directly-controlled BJTs
2019-04-17 added volume control input
2019-04-17 created MCP4725 on schematic
2019-04-18 Finished V1 of schematic
2019-04-19 added resistor values for SPI Switch
2019-04-20 generated part list
2019-04-20 minor tweaks to aid finding parts for prototype
2019-05-22 Bringing repo up-to-date with PWM and MCP4725 DAC tests
2019-05-24 Sound finally works, Reaper says "next"
2019-05-27 Playing sound from SPI Flash now works
2019-05-28 boosted MCU frequency to 20MHz, optimized sound loop
2019-05-30 uni-directional communication tested and working
2019-05-31 bidirectional communication with nRF24L01 on same SPI bus as flash
2019-06-02 Simplified Schematic
2019-06-04 finished schematic, working on laying out pcb
2019-06-04 Started adding footprints to PCB
2019-06-06 power and audio traces routed
2019-06-06 moved flash to backside of board
2019-06-06 Finished board layout, adding graphics
2019-06-06 Added nameplate
2019-06-06 added pcb info
2019-06-20 Flipped PCB Tray to match manufactured PCB
2019-06-20 Final Gerber files for manufacture
2019-07-16 modified tests for finished board to ensure proper PCB layout
2019-07-17 added trigger switch test
2019-07-21 Added missing trigger
2019-07-24 Added trigger and migrated STM32 project to production workspace
2019-07-25 preliminary attempt at master/slave dynamic pairing
2019-07-25 added pin labels
2019-07-25 rejigged GPIO_PIN_X labels to user-defined
2019-07-25 bare-minimum functional demo working
2019-07-29 implemented dynamic channels... 4 boards have been tested to pair in 2's
2019-07-29 Made Channel 0 the pairing channel, and made channel selection exclude 0
2019-07-30 voice lines added and tested working at reload
2019-07-30 Optimized code and added better comments
2019-08-08 Fixed back of STL
2019-08-09 fixed boolean issue with "butt"
2019-08-09 simplified and updated parts to match working file
2019-08-11 Created a box to ship the PCB boards in safely
2019-08-11 Added holes for screws to secure top to bottom
2019-08-11 staged for printing
2019-08-12 Added missing part of Barrel B
2019-08-18 fixed smoothing on rough side
2019-08-22 language settings
2019-08-22 brought decorative piece into its own file for print tests
2019-08-22 view change in shipping container
2019-08-22 Added Armor pieces
2019-08-22 Added reference images we've been working off of
2019-08-22 fixed in 3d builder
2019-08-22 inverted head to cut down print time and material
2019-08-23 flipped normals to fix support structures
2019-08-23 Added a visual scale reference image
2019-08-23 new size emblem
2019-08-23 used scaled image to get correct size emblem
2019-08-24 Belt Case files
2019-08-24 leveled for printing
2019-08-25 added belt buckle parts for printing
2019-08-25 working file for belt buckle parts and animation
2019-08-26 fixed screw hole size, screw hole depth, and magnet hole size
2019-08-28 Created the "ring" for one of Reaper's belts
2019-08-28 added new reference image for details for guns
2019-08-29 working files for belt details
2019-08-29 Belt Fastener Printable Files
2019-09-02 added armor for left arm
2019-09-03 Staged Left Fingertip Covers for printing
2019-09-03 Added right fingertip covers
2019-09-03 Staged Right Thumb Cover for print
2019-09-04 Left Gauntlet Pieces
2019-09-04 Right Gauntlet Pieces
2019-09-04 Working files for hand/arm armor
2019-09-04 fixed normals in 3d builder
2019-09-04 Removed vestigial parts of horns, & made butt thic
2019-09-04 Settled model to ensure adhesion to bed
2019-09-05 Working files for right gauntlet pieces
2019-09-05 Modeled right hand cover
2019-09-08 increased curve and slightly decreased size
2019-09-08 Added mounting points for elastic
2019-09-09 improved structural integrity of elastic through-holes
2019-09-11 Modeled missing part for heel of boot
2019-09-11 Adjusted sizing of boot parts to fit
2019-09-11 Modeled missing part for back of boot
2019-09-12 Sized spike to match hand cover
2019-09-13 Enlarged to accomodate paint
2019-09-13 Resized head to accomodate paint
2019-09-13 created 3d model of boot and fitted parts to it
2019-09-13 updates to working files
2019-09-13 made cap shorter to improve accuracy to costume
2019-09-14 fixed barrel length to reflect character design
2019-09-14 Made interior diameter of cap smaller
2019-09-18 Split Calf Covers differently to allow for magnets
2019-09-18 Split Calf Cover tops into 8 pieces to facilitate printing
2019-09-19 Resized calf cover to fit ankle
2019-09-20 Attempted to fix relative scale issues by exporting again
2019-09-20 Fixed and rotated 180 degrees in 3d builder
2019-09-24 Modifications based on having physical components in-hand
2019-09-24 Widened cavity for batteries
2019-09-24 Decreased size of trigger for better travel
2019-09-24 Increased size of battery cavity
2019-09-24 Pegs are now attached to tray
2019-09-25 Mirrored left pieces to right
2019-09-25 Made trigger pivot hole smaller
2019-10-06 flipped upside-down for better print time
2019-10-07 Changes in resizing calf cover top parts to fit
2019-10-07 flipped upside down to make printing easier
2019-10-07 increased size to match revised top parts
2019-10-12 assembled to-print files to ensure fit
2019-10-29 Fixed link to dual-spi device test video
2019-11-04 Made vertical to facilitate higher quality printing
2019-11-07 broke out second decorative piece, renamed first
